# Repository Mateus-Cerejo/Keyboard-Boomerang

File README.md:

# Boomerang
A split, wireless, low profile keyboard. Inspired by the [Corne](https://github.com/foostan/crkbd) and [Caldera](https://github.com/christianselig/caldera-keyboard).

**ATENTION** SOME FILES ARE STILL MISSING OR STILL NEED TO BE UPDATED. DON'T ATTEMPT THIS YET.

Temporary image of the outline

## Tutorial
### Material list
Besides the soldering equipment, you will need:

- Case x2 - [files](/case/)
- Switch plate x2 - [files](/case/)
- PCB x2 - [gerbers](/gerbers/) / [pcb](/pcbs/)
- Pro Micro nRF52840 [or similar](https://github.com/joric/nrfmicro/wiki/Alternatives) x2
- Choc V1 switches x38
- Choc V1 keycaps x38
- Lithium-ion batteries x2
- Spacers M3 8mm x14
- Screws M3 6mm x28
- On / Off switch (SS-12D00) x2
- Reset button x2
- Rubber bumpers x8

### Steps

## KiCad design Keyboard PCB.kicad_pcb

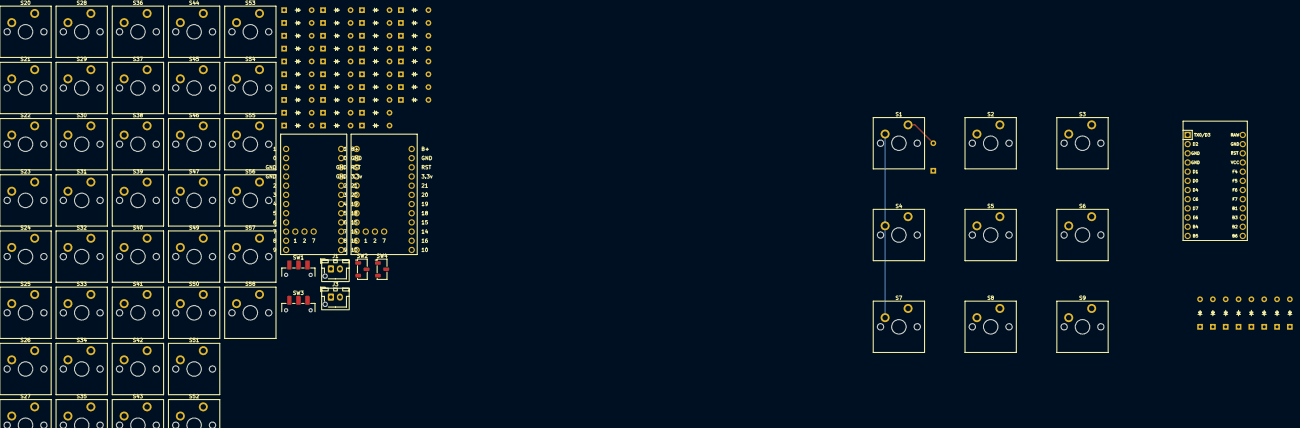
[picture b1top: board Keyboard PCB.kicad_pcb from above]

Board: 2 copper layers, 103 parts (1 on the bottom side), 83 nets.

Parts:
D1, D2, D3, D4, D5, D6, D7, D8, D9, D20, D21, D22, D23, D24, D25, D26, D27, D28, D29, D30, D31, D32, D33, D34, D35, D36, D37, D38, D39, D40, D41, D42, D43, D44, D45, D46, D47, D49, D50, D51, D52, D53, D54, D55, D56, D57, D58: Diode_DO-35
J1: Battery Right; JST_XH_B2B-XH-AM_1x02_P2.50mm_Vertical
J3: Battery Left; JST_XH_B2B-XH-AM_1x02_P2.50mm_Vertical
S1, S2, S3, S4, S5, S6, S7, S8, S9, S20, S21, S22, S23, S24, S25, S26, S27, S28, S29, S30, S31, S32, S33, S34, S35, S36, S37, S38, S39, S40, S41, S42, S43, S44, S45, S46, S47, S49, S50, S51, S52, S53, S54, S55, S56, S57, S58: MX_PCB_1.00u
SW1, SW3: SW_SPST; SW_SPDT_CK_JS102011SAQN
SW2, SW4: SW_Push; Nidec_Copal_CAS-120A
U1: Arduino_Pro_Micro
U2, U5: Nice_Nano_V2

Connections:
Column 0: S1.1, S4.1, S7.1, U1.5 (2/PD1)
Column 1: S2.1, S5.1, S8.1, U1.6 (3/PD0)
Column 2: S3.1, S6.1, S9.1, U1.7 (4/PD4)
Left B+: SW3.2 (B), U5.24 (B+)
Left Column 1: S34.1, U5.11 (8)
Left Column 2: S35.1, S36.1, S37.1, S54.1, S55.1, U5.12 (9)
Left Column 3: S38.1, S39.1, S40.1, S56.1, U5.20 (21)
Left Column 4: S41.1, S42.1, S43.1, S57.1, U5.19 (20)
Left Column 5: S44.1, S45.1, S46.1, S58.1, U5.18 (19)
Left Column 6: S47.1, U5.17 (18)
Left Ground: J3.2, SW4.2, U5.3 (GND), U5.4 (GND), U5.23 (GND)
Left Reset: SW4.1, U5.22 (RST)
Left Row 1: D35.1 (K), D38.1 (K), D41.1 (K), D44.1 (K), U5.5 (2)
Left Row 2: D34.1 (K), D36.1 (K), D39.1 (K), D42.1 (K), D45.1 (K), D47.1 (K), U5.6 (3)
Left Row 3: D37.1 (K), D40.1 (K), D43.1 (K), D46.1 (K), U5.7 (4)
Left Row 4: D54.1 (K), D56.1 (K), D57.1 (K), D58.1 (K), U5.8 (5)
Left Row 5: D55.1 (K), U5.9 (6)
unnamed: D1.2 (A), S1.2
unnamed: D2.2 (A), S2.2
unnamed: D3.2 (A), S3.2
unnamed: D4.2 (A), S4.2
unnamed: D5.2 (A), S5.2
unnamed: D6.2 (A), S6.2
unnamed: D7.2 (A), S7.2
unnamed: D8.2 (A), S8.2
unnamed: D9.2 (A), S9.2
unnamed: D20.2 (A), S20.2
unnamed: D21.2 (A), S21.2
unnamed: D22.2 (A), S22.2
unnamed: D23.2 (A), S23.2
unnamed: D24.2 (A), S24.2
unnamed: D25.2 (A), S25.2
unnamed: D26.2 (A), S26.2
unnamed: D27.2 (A), S27.2
unnamed: D28.2 (A), S28.2
unnamed: D29.2 (A), S29.2
unnamed: D30.2 (A), S30.2
unnamed: D31.2 (A), S31.2
unnamed: D32.2 (A), S32.2
unnamed: D33.2 (A), S33.2
unnamed: D34.2 (A), S34.2
unnamed: D35.2 (A), S35.2
unnamed: D36.2 (A), S36.2
unnamed: D37.2 (A), S37.2
unnamed: D38.2 (A), S38.2
unnamed: D39.2 (A), S39.2
unnamed: D40.2 (A), S40.2
unnamed: D41.2 (A), S41.2
unnamed: D42.2 (A), S42.2
unnamed: D43.2 (A), S43.2
unnamed: D44.2 (A), S44.2
unnamed: D45.2 (A), S45.2
unnamed: D46.2 (A), S46.2
unnamed: D47.2 (A), S47.2
unnamed: D49.2 (A), S49.2
unnamed: D50.2 (A), S50.2
unnamed: D51.2 (A), S51.2
unnamed: D52.2 (A), S52.2
unnamed: D53.2 (A), S53.2
unnamed: D54.2 (A), S54.2
unnamed: D55.2 (A), S55.2
unnamed: D56.2 (A), S56.2
unnamed: D57.2 (A), S57.2
unnamed: D58.2 (A), S58.2
unnamed: J1.1, SW1.1 (A)
unnamed: J3.1, SW3.1 (A)
Right B+: SW1.2 (B), U2.24 (B+)
Right Column 1: S20.1, U2.11 (8)
Right Column 2: S21.1, S26.1, S30.1, S49.1, S53.1, U2.12 (9)
Right Column 3: S22.1, S27.1, S31.1, S50.1, U2.20 (21)
Right Column 4: S23.1, S28.1, S32.1, S51.1, U2.19 (20)
Right Column 5: S24.1, S29.1, S33.1, S52.1, U2.18 (19)
Right Column 6: S25.1, U2.17 (18)
Right Ground: J1.2, SW2.2, U2.3 (GND), U2.4 (GND), U2.23 (GND)
Right Reset: SW2.1, U2.22 (RST)
Right Row 1: D26.1 (K), D27.1 (K), D28.1 (K), D29.1 (K), U2.5 (2)
Right Row 2: D20.1 (K), D21.1 (K), D22.1 (K), D23.1 (K), D24.1 (K), D25.1 (K), U2.6 (3)
Right Row 3: D30.1 (K), D31.1 (K), D32.1 (K), D33.1 (K), U2.7 (4)
Right Row 4: D49.1 (K), D50.1 (K), D51.1 (K), D52.1 (K), U2.8 (5)
Right Row 5: D53.1 (K), U2.9 (6)
Row 0: D1.1 (K), D2.1 (K), D3.1 (K), U1.8 (5/PC6)
Row 1: D4.1 (K), D5.1 (K), D6.1 (K), U1.9 (6/PD7)
Row 2: D7.1 (K), D8.1 (K), D9.1 (K), U1.10 (7/PE6)

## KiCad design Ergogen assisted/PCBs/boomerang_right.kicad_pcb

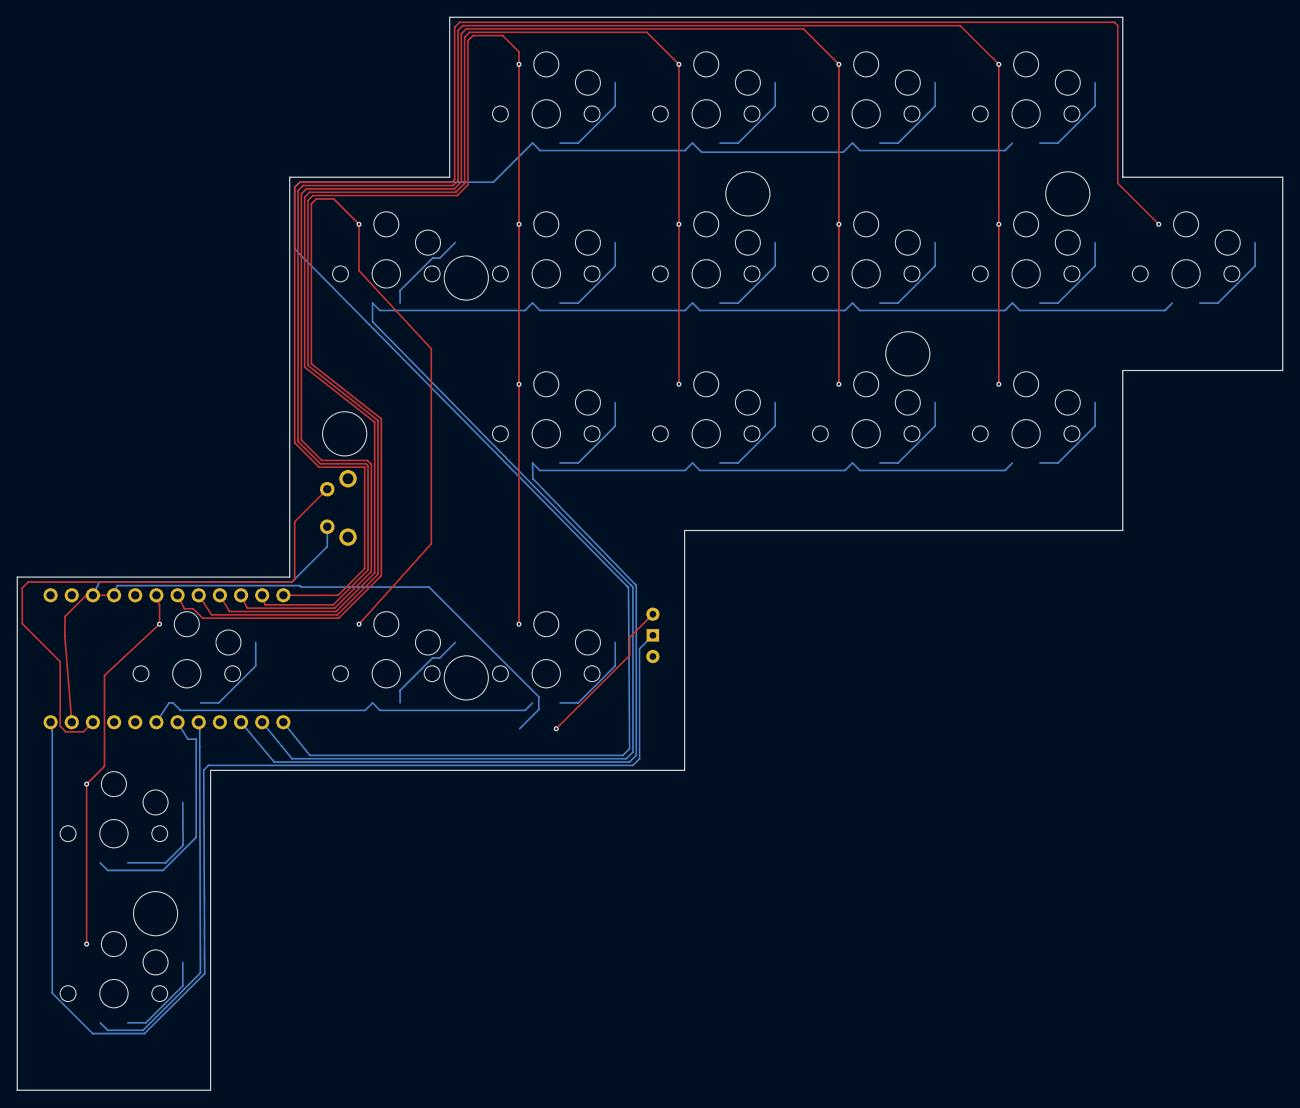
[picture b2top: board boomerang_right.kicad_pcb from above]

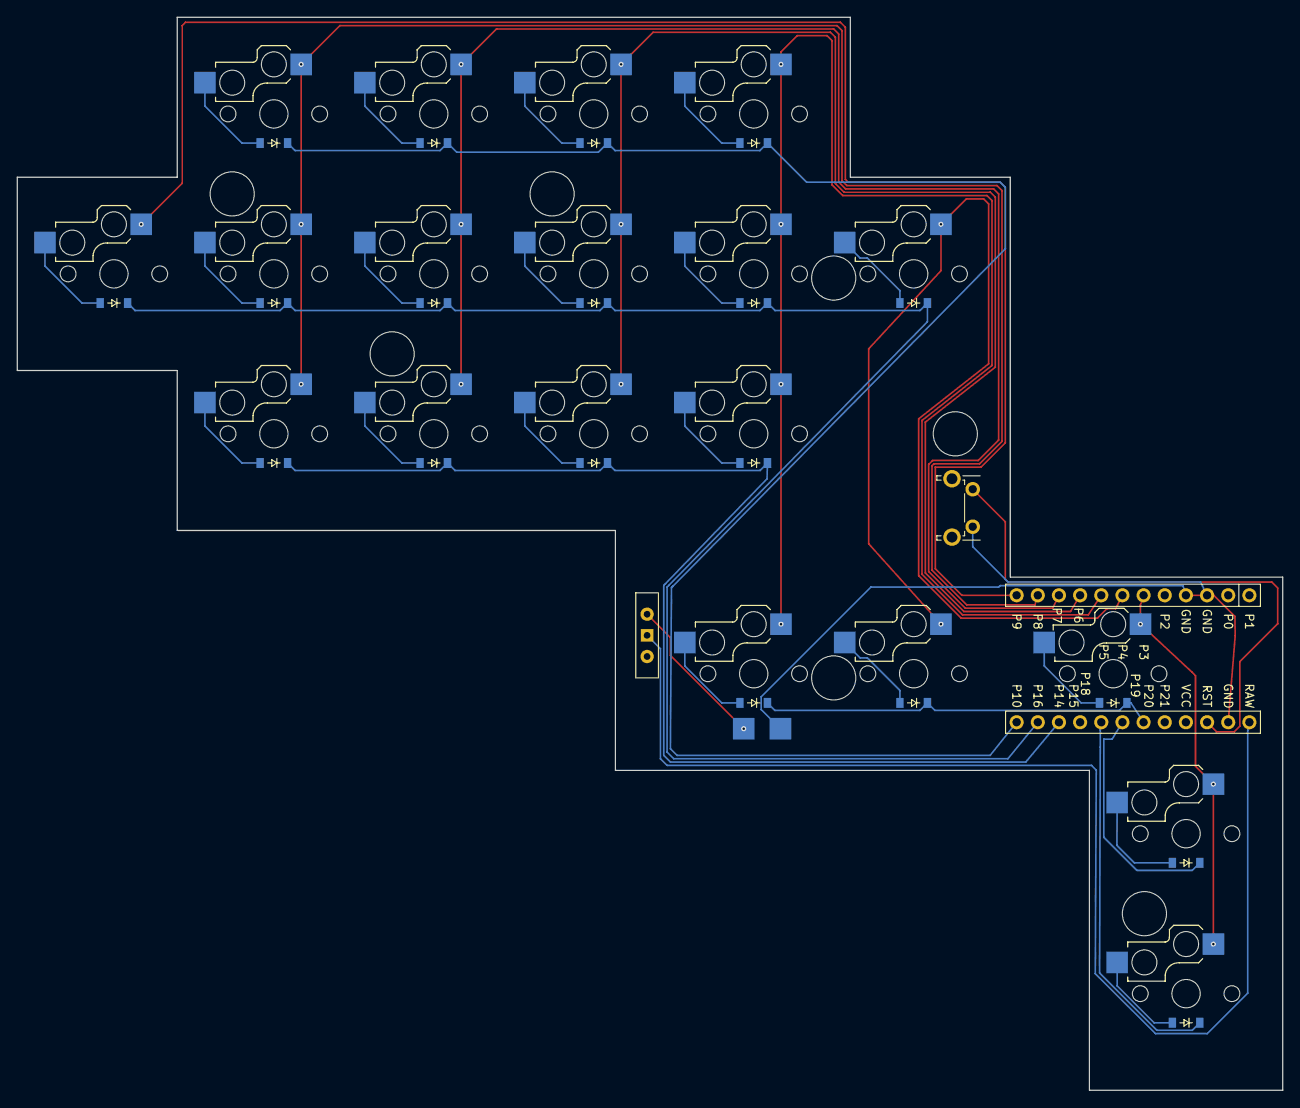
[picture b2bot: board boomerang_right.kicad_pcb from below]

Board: 2 copper layers, 151.9 x 128.8 mm, 46 parts (39 on the bottom side), 33 nets.

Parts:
D1, D2, D3, D4, D5, D6, D7, D8, D9, D10, D11, D12, D13, D14, D15, D16, D17, D18, D19: diode_tht_sod123
MCU1: mcu_nice_nano
MH1, MH3, MH5, MH6, MH7, MH8, MH10: mounting_hole_npth
S1, S2, S3, S4, S5, S6, S7, S8, S9, S10, S11, S12, S13, S14, S15, S16, S17, S18, S19: switch_choc_v1_v2

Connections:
GND: MCU1.3, MCU1.4, MCU1.23
P3: MCU1.6, S15.1, S16.1, S17.1
P4: MCU1.7, S1.1, S18.1
P5: MCU1.8, S2.1, S3.1, S4.1, S19.1
P6: MCU1.9, S5.1, S6.1, S7.1
P7: MCU1.10, S8.1, S9.1, S10.1
P8: MCU1.11, S11.1, S12.1, S13.1
P9: MCU1.12, S14.1
P10: D4.1, D7.1, D10.1, D13.1, MCU1.13
P14: D2.1, D5.1, D8.1, D11.1, MCU1.15
P16: D1.1, D3.1, D6.1, D9.1, D12.1, D14.1, MCU1.14
P18: D15.1, MCU1.17
P19: D16.1, MCU1.18
P20: D17.1, D18.1, D19.1, MCU1.19
index_bottom: D2.2, S2.2
index_middle: D3.2, S3.2
index_top: D4.2, S4.2
left_bottom: D16.2, S16.2
left_middle: D1.2, S1.2
left_rockBottom: D15.2, S15.2
left_top: D17.2, S17.2
mid_top: D18.2, S18.2
middle_bottom: D5.2, S5.2
middle_middle: D6.2, S6.2
middle_top: D7.2, S7.2
pinky_bottom: D11.2, S11.2
pinky_middle: D12.2, S12.2
pinky_top: D13.2, S13.2
right_middle: D14.2, S14.2
right_top: D19.2, S19.2
ring_bottom: D8.2, S8.2
ring_middle: D9.2, S9.2
ring_top: D10.2, S10.2

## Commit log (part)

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2026-04-20 feat: Schematic for Keyboard
2026-04-25 chore: Updated .gitignore
2026-04-25 style: Center schematics and increase sheet size
2026-05-31 Ergogen assited PCBs
    Uses stock footprints from ergogen and kicad with some slight modifications.
    zip is for ergogen.xyz
2026-06-14 feat: Gerbers
2026-06-14 fix: PCBs fixed positions
2026-06-14 chore: moved
2026-06-14 feat: Shopping list
2026-06-14 fix: PCBs positions
